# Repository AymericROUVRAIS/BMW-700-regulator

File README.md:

# BMW 700 regulator
This is a modern replacement of B6-08-0060 and B7-18-0600

---

The PCB can be found in the gerble file. Schematics are in the pdf file, in this file there are also the original BMW 700 documents.

The electronics used are :
- Voltage regulator *LM393*
- Mosfet
- TVS diode
- Zener diode
- Freewheling diode 
- Relay
- Resistors *10k* and *100* ohms
- Capacitor *100nF*

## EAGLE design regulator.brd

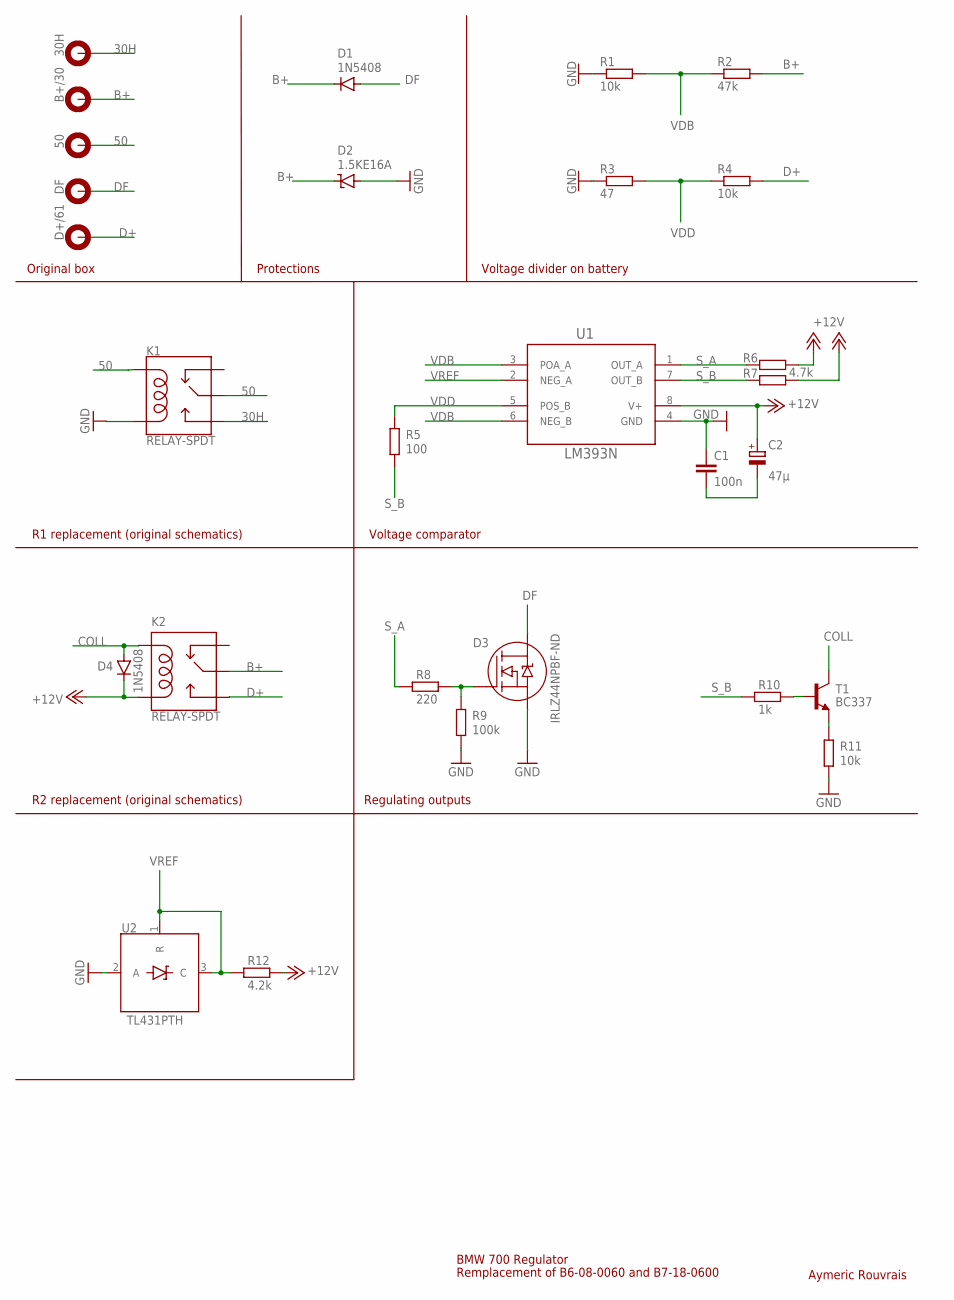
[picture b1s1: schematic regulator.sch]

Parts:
30H, 50: MOUNT-PAD-ROUND3.0; 3,0-PAD
B+/30: MOUNT-PAD-ROUND3.0; 3,0-PAD
C1: 100n; C050-025X075
C2: 47µ; E2,5-7
D1, D4: 1N5408
D2: 1.5KE16A
D3: IRLZ44NPBF-ND; TO220AB
D+/61: MOUNT-PAD-ROUND3.0; 3,0-PAD
DF: MOUNT-PAD-ROUND3.0; 3,0-PAD
K1, K2: RELAY-SPDT; RELAY_G5LE
R1, R4, R11: 10k; 0204/7
R2: 47k; 0204/7
R3: 47; 0204/7
R5: 100; 0204/7
R6, R7: 4.7k; 0204/7
R8: 220; 0204/7
R9: 100k; 0204/7
R10: 1k; 0204/7
R12: 4.2k; 0204/7
T1: BC337; TO92
U1: LM393N; DIP254P762X508-8
U2: TL431PTH; TO-92

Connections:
30H: 30H.B3,0, K1.3 (NO)
50: 50.B3,0, K1.1 (MAIN), K1.2 (COIL1)
+12V: C2.+, D4.1 (C), K2.5 (COIL2), R6.2, R7.2, R12.2, U1.8 (V+)
B+: B+/30.B3,0, D1.1 (C), D2.1 (C), K2.1 (MAIN), R2.2
COLL: D4.2 (A), K2.2 (COIL1), T1.3 (C)
D+: D+/61.B3,0, K2.3 (NO), R4.2
DF: D1.2 (A), D3.1 (D), DF.B3,0
GND: C1.1, D2.2 (A), D3.3 (S), K1.5 (COIL2), R1.1, R3.1, R9.2, R11.1, U1.4 (GND), U2.2 (A)
unnamed: D3.2 (G), R8.2, R9.1
unnamed: R10.2, T1.2 (B)
unnamed: R11.2, T1.1 (E)
unnamed: C1.2, C2.-
S_A: R6.1, R8.1, U1.1 (OUT_A)
S_B: R5.1, R7.1, R10.1, U1.7 (OUT_B)
VDB: R1.2, R2.1, U1.3 (POA_A), U1.6 (NEG_B)
VDD: R3.2, R4.1, R5.2, U1.5 (POS_B)
VREF: R12.1, U1.2 (NEG_A), U2.1 (R), U2.3 (C)

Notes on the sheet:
BMW 700 Regulator
Remplacement of B6-08-0060 and B7-18-0600
Aymeric Rouvrais
Original box
Protections
R1 replacement (original schematics)
R2 replacement (original schematics)
Voltage divider on battery
Voltage comparator
Regulating outputs

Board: 2 copper layers, 28 parts (1 on the bottom side), 17 nets, no tracks yet.

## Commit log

2026-06-16 Adding initial information to README
2026-06-19 Adding electronics schematics and project
2026-06-19 Adding original schematics
2026-06-19 Adding .gitignore
2026-06-19 Adding schematic
2026-06-19 Removing compilation files for the board schematics
2026-06-19 Completed the schematics
2026-06-19 Creating the circuit board

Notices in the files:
parts and their libraries:
SparkFun-Electromechanical: Licensing: Creative Commons ShareAlike 4.0 International - https://creativecommons.org/licenses/by-sa/4.0
